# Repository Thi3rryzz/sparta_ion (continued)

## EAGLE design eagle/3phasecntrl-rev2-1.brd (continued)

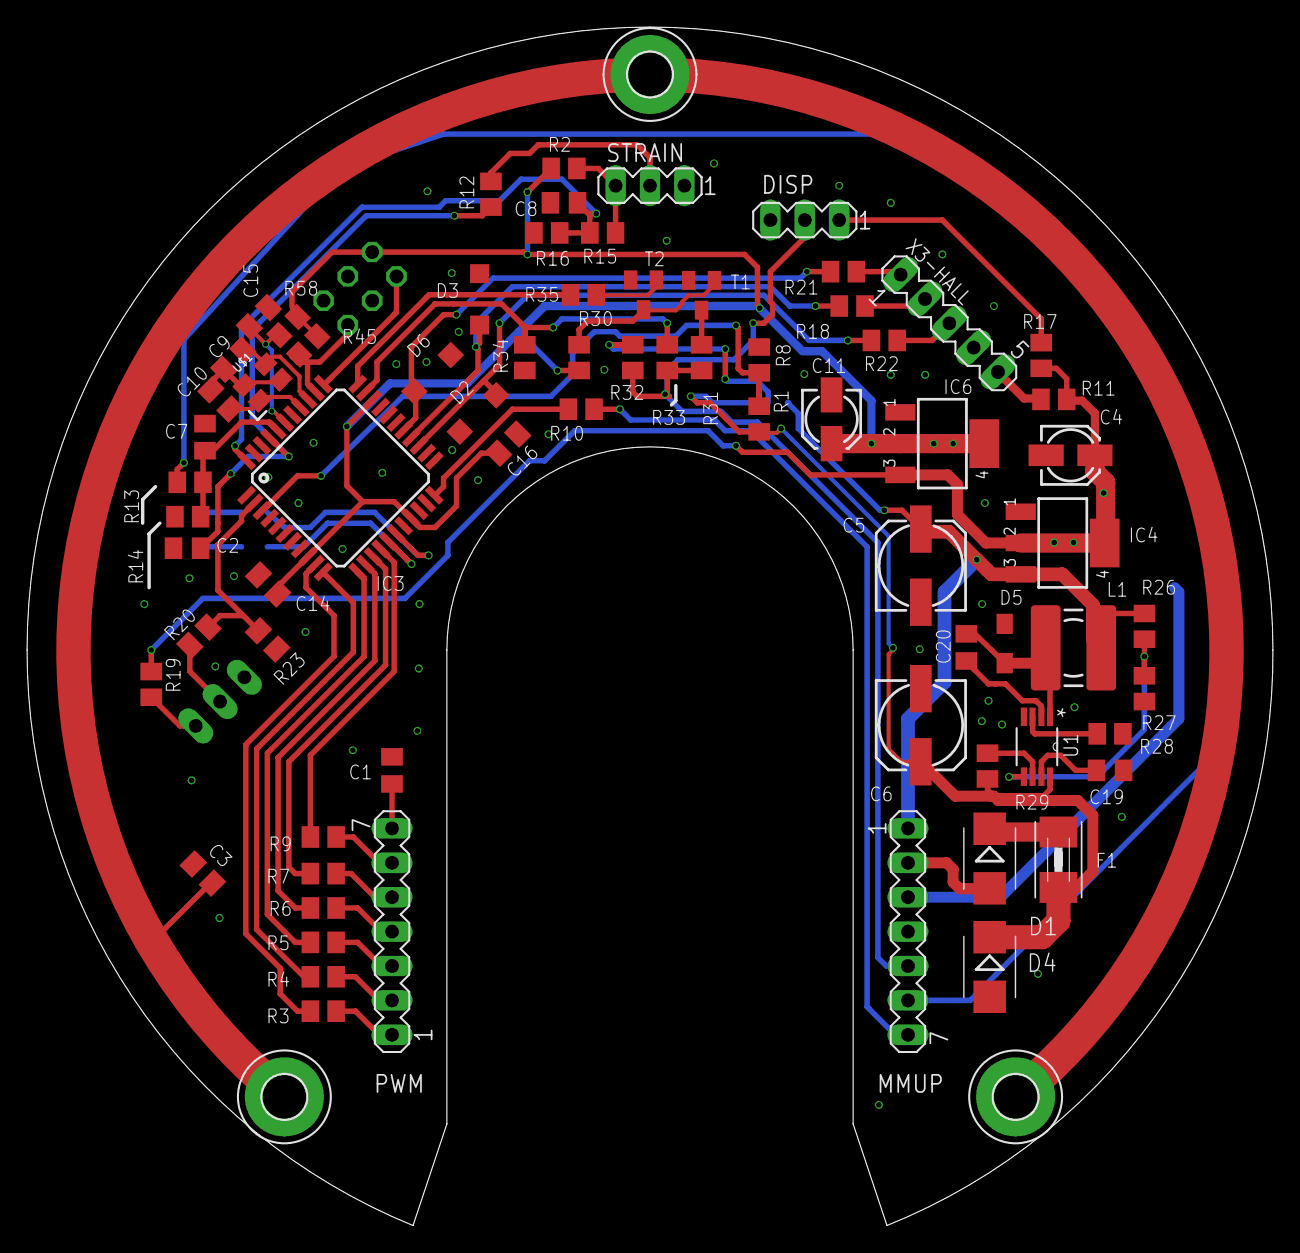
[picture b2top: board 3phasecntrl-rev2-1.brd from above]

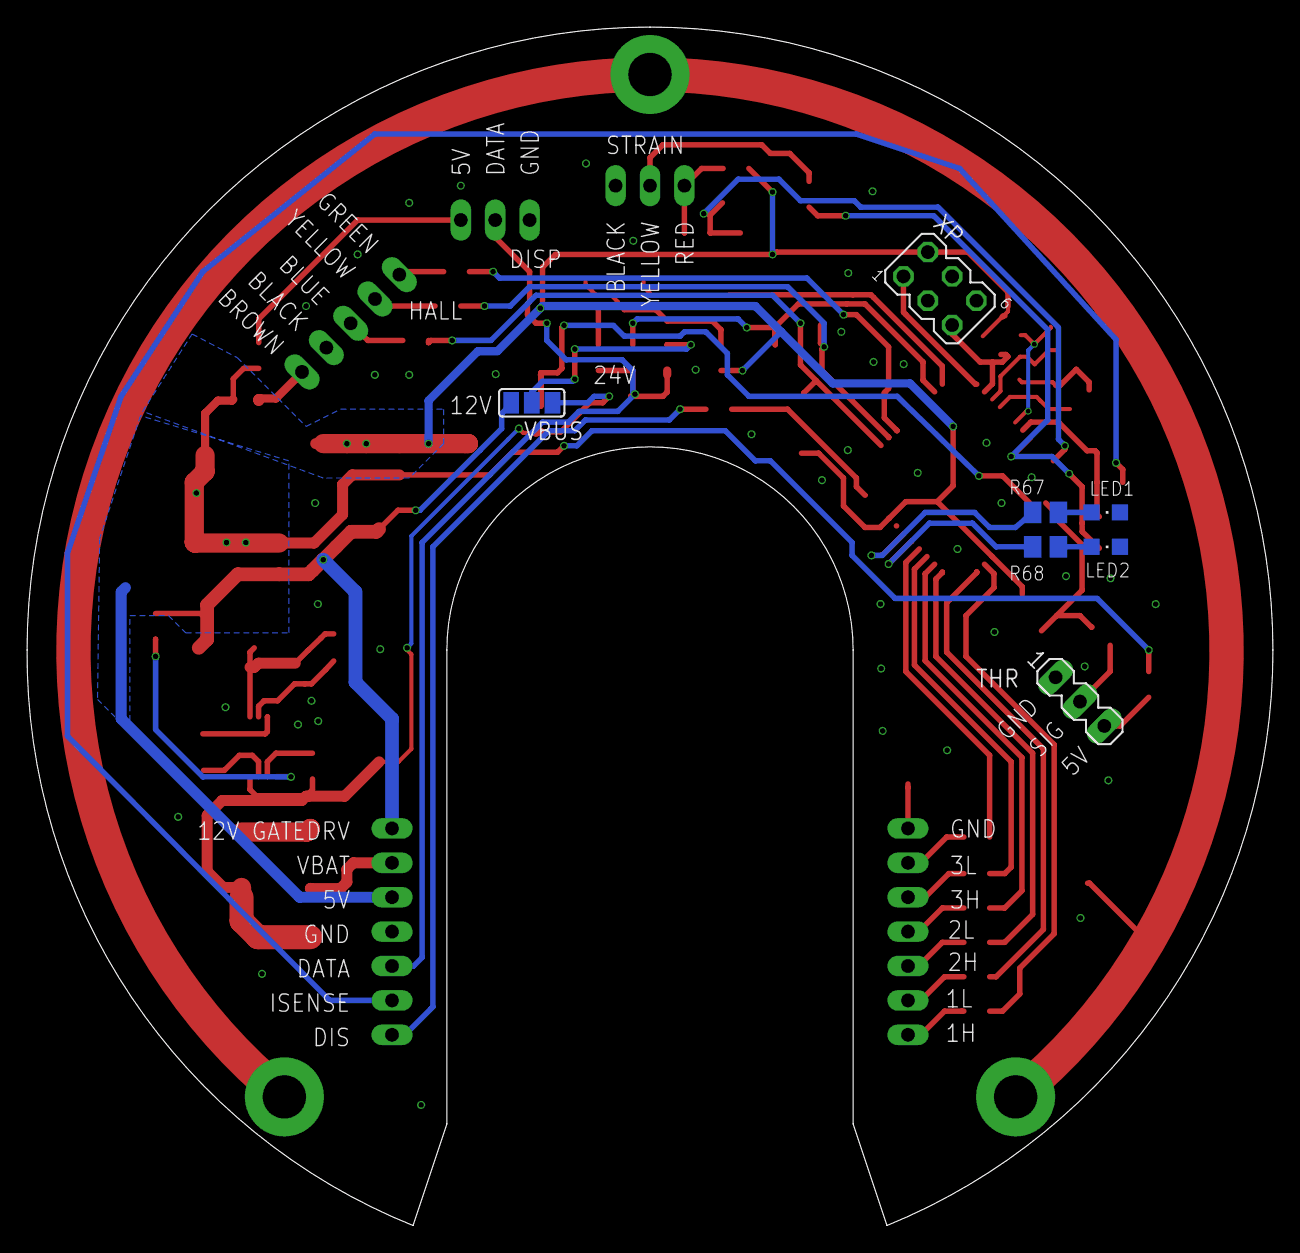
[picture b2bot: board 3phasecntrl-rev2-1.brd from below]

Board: 2 copper layers, 92.0 x 88.5 mm, 81 parts (7 on the bottom side), 63 nets.

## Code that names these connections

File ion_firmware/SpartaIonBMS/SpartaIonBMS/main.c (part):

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 * Author : T. Ligeon
 *	
 *  BQ34Z100 = C0/C1
 *	BOW_UART = PE2/PE3
 *	RTC I2C = PE0/PE1
 */ 

// Defines
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//Initialize all IO.
void _init_GPIO(void){
	
	PORTA.DIRCLR = MIDPOINT_V_PIN | VIN_SENSE_PIN | CHG_PRESENT_PIN | PACK_TEMP_PIN | PCB_TEMP_PIN;
	PORTC.DIRCLR = BQ34Z100_ALERT_PIN;
	PORTC.DIRSET = LIGHT_EN_PIN | MOT_PWR_EN_PIN | CHG_PWR_EN_PIN | LED1_PIN | LED2_PIN | SDA_C_PIN | SCL_C_PIN;
	PORTD.DIRCLR = RTC_INT_PIN;	
	PORTE.DIRSET = SDA_E_PIN | SCL_E_PIN | BOW_TX_PIN;
	PORTE.DIRCLR = BOW_RX_PIN;
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	_delay_ms(500);
	LED2_PORT.OUTCLR = LED2_PIN;
	_delay_ms(500);
	MOT_PWR_EN_PORT.OUTSET = MOT_PWR_EN_PIN;
	_delay_ms(500);
	MOT_PWR_EN_PORT.OUTCLR = MOT_PWR_EN_PIN;
	_delay_ms(500);
	CHG_PWR_EN_PORT.OUTSET = CHG_PWR_EN_PIN;
	_delay_ms(500);
	CHG_PWR_EN_PORT.OUTCLR = CHG_PWR_EN_PIN;
	_delay_ms(500);
}

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bowStrSize = snprintf(bow_buffer, 1024 ,"FuelGauge Optimization Cycle\r\n Start discharging until 19.8V...\r\n");
bus_send(&bus, (uint8_t*) bow_buffer, bowStrSize);
while(bus_isbusy(&bus) == 0){};
MOT_PWR_EN_PORT.OUTSET= MOT_PWR_EN_PIN;
LED2_PORT.OUTSET = LED2_PIN;
while(bqData.packVoltage >= 19800){
	_update_FuelGauge();
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	while(bus_isbusy(&bus) == 0){};
	_delay_ms(5000);
}
MOT_PWR_EN_PORT.OUTCLR= MOT_PWR_EN_PIN;
LED2_PORT.OUTCLR = LED2_PIN;
bowStrSize = snprintf(bow_buffer, 1024 ,"Discharging Done. Wait	until VOK and RUP_DIS are cleared.\r\n");
bus_send(&bus, (uint8_t*) bow_buffer, bowStrSize);
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	while(bus_isbusy(&bus) == 0){};
	_delay_ms(5000);
}
CHG_PWR_EN_PORT.OUTCLR = CHG_PWR_EN_PIN;
LED1_PORT.OUTCLR = LED1_PIN;
bowStrSize = snprintf(bow_buffer, 1024 ," Full charge detected!\r\n");
bus_send(&bus, (uint8_t*) bow_buffer, bowStrSize);
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bowStrSize = snprintf(bow_buffer, 1024 ,"Start Discharge again\r\n");
bus_send(&bus, (uint8_t*) bow_buffer, bowStrSize);
while(bus_isbusy(&bus) == 0){};
MOT_PWR_EN_PORT.OUTSET= MOT_PWR_EN_PIN;
LED2_PORT.OUTSET = LED2_PIN;
while(bqData.packVoltage >= 19700){
	_update_FuelGauge();
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	while(bus_isbusy(&bus) == 0){};
	_delay_ms(5000);
}
MOT_PWR_EN_PORT.OUTCLR= MOT_PWR_EN_PIN;
LED2_PORT.OUTCLR = LED2_PIN;
bowStrSize = snprintf(bow_buffer, 1024 ,"Discharge Complete, Starting 5 hour wait again\r\n");
bus_send(&bus, (uint8_t*) bow_buffer, bowStrSize);
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	//green_led_on();
	//motor_on();
	//while(1){}
	//MOT_PWR_EN_PORT.OUTSET = MOT_PWR_EN_PIN;
	//display.online = true;
	//TCC1_CTRLA = TC_CLKSEL_OFF_gc;
	// (Print) Starting Fuel Gauge Info:
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
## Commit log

2020-07-06 Hexfile Linecount initialization mem error
2020-07-06 Converted main ION-MD firmware to Atmel Studio 7
2020-07-07 Added python BOW Sniff Script for CU3 Testing
2020-07-07 3phasecntrl-rev-2-1 added. Crystal bijgebeund
2020-07-08 Voltage working on CU3, Current To be verified
2020-07-21 Semi-Usable CU3, Baud also increased to 19200
2020-08-01 Added rev1.0 of Banana BMS.
2020-08-02 Update README.md and added Discord link.
2021-02-17 Add BMS to Bootloader and 16MHz crystal.
2021-02-17 Add initial Semi-Working BMS firmware
2021-02-17 More CU3 functions added
2021-02-17 Support 16MHz external crystal.
2021-02-17 Add BMS to bootloader
2021-02-17 Modified project file
